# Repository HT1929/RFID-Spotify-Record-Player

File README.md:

# RFID-Spotify-Record-Player
Instead of vinyl records, RFID chips embedded in custom-made mini-records will trigger specific Spotify songs via a Raspberry Pi. The system mimics the action of placing a record on a turntable, offering both a visual spinning effect and the vast music library of Spotify.

# Project Overview
The RFID Spotify Record Player allows users to:
- Play, pause, skip and control volume for Spotify tracks.
- Select songs or playlists through a physical interface using the RFID sensor.
- Output audio through a built-in speaker system.
- Watch a disk spin as if it were playing a vinyl record, adding to the aesthetic of a traditional record player.

# Features
**User Interface:** Physical controls for playback and navigation.

**Controller:** Manages user inputs and communicates with Spotify.

**Network Module:** Connects to Wi-Fi to access the Spotify API.

**Spinning Disk:** A motorized disk spins to mimic the look of a record on a turntable.

**Spotify Integration:** Streams music directly from Spotify using the Spotify API.

**Audio Output:** Plays audio through connected speakers.

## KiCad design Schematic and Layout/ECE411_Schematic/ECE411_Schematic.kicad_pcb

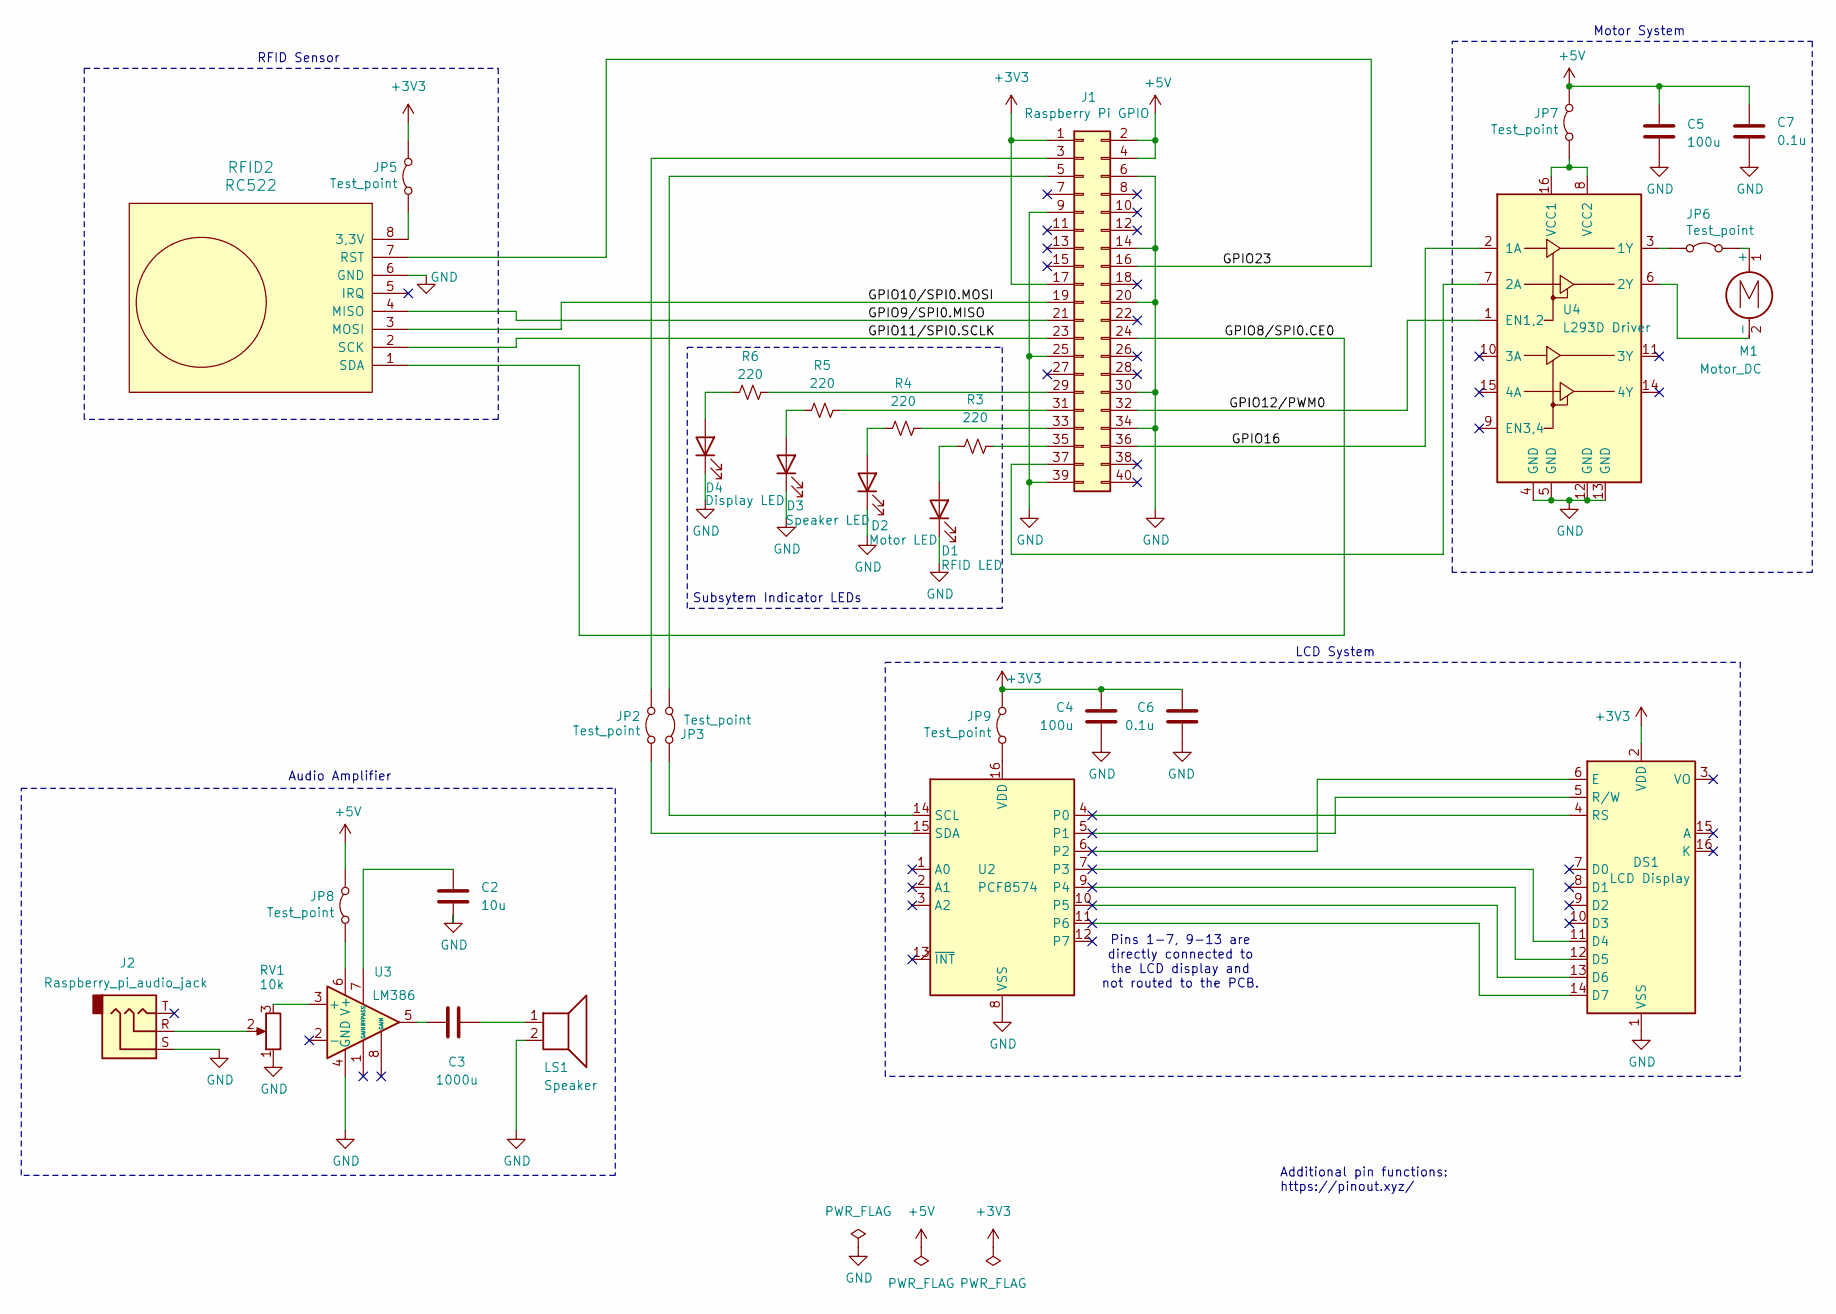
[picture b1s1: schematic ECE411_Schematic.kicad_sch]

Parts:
C2: 10u; C_Radial_D5.0mm_H11.0mm_P2.00mm
C3: 1000u; C_Radial_D10.0mm_H20.0mm_P5.00mm
C4, C5: 100u; C_0805_2012Metric_Pad1.18x1.45mm_HandSolder
C6, C7: 0.1u; C_0805_2012Metric_Pad1.18x1.45mm_HandSolder
D1: RFID LED; LED_Yuji_5730
D2: Motor LED; LED_Yuji_5730
D3: Speaker LED; LED_Yuji_5730
D4: Display LED; LED_Yuji_5730
DS1: LCD Display
J1: Raspberry Pi GPIO; PinSocket_2x20_P2.54mm_Vertical
J2: Raspberry_pi_audio_jack
JP2, JP3, JP5, JP6, JP7, JP8, JP9: Test_point; R_Axial_DIN0204_L3.6mm_D1.6mm_P2.54mm_Vertical
LS1: Speaker
M1: Motor_DC; Motor
R3, R4, R5, R6: 220; R_0805_2012Metric_Pad1.20x1.40mm_HandSolder
RFID2: RC522
RV1: 10k; Potentiometer_Bourns_3299W_Vertical
U2: PCF8574; LCD1602
U3: LM386; DIP-8_W7.62mm
U4: L293D Driver; DIP-16_W7.62mm

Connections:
+3V3: C4.1, C6.1, DS1.2 (VDD), J1.1, J1.17, JP5.2 (B), JP9.2 (B)
+5V: C5.1, C7.1, J1.2, J1.4, JP7.2 (B), JP8.2 (B)
/GPIO8/SPI0.CE0: J1.24, RFID2.1 (SDA); also elsewhere on the board
/GPIO9/SPI0.MISO: J1.21, RFID2.4 (MISO); also elsewhere on the board
/GPIO10/SPI0.MOSI: J1.19, RFID2.3 (MOSI); also elsewhere on the board
/GPIO11/SPI0.SCLK: J1.23, RFID2.2 (SCK); also elsewhere on the board
/GPIO12/PWM0: J1.32, U4.1 (EN1,2)
/GPIO16: J1.36, U4.2 (1A)
/GPIO23: J1.16, RFID2.7 (RST); also elsewhere on the board
GND: C2.2, C4.2, C5.2, C6.2, C7.2, D1.1 (K), D2.1 (K), D3.1 (K), D4.1 (K), DS1.1 (VSS), J1.6, J1.9, J1.14, J1.20, J1.25, J1.30, J1.34, J1.39, J2.S, LS1.2, RFID2.6 (GND), RV1.1, U2.8 (VSS), U3.4 (GND), U4.4 (GND), U4.5 (GND), U4.12 (GND), U4.13 (GND); also elsewhere on the board
unnamed: C3.1, U3.5
unnamed: C3.2, LS1.1
unnamed: D1.2 (A), R3.1
unnamed: D2.2 (A), R4.1
unnamed: D3.2 (A), R5.1
unnamed: D4.2 (A), R6.1
unnamed: DS1.4 (RS), U2.4 (P0)
unnamed: DS1.5 (R/W), U2.5 (P1)
unnamed: DS1.6 (E), U2.6 (P2)
unnamed: DS1.11 (D4), U2.7 (P3)
unnamed: DS1.12 (D5), U2.9 (P4)
unnamed: DS1.13 (D6), U2.10 (P5)
unnamed: DS1.14 (D7), U2.11 (P6)
unnamed: J1.3, JP2.2 (B)
unnamed: J1.5, JP3.1 (A)
unnamed: J1.29, R6.2
unnamed: J1.31, R5.2
unnamed: J1.33, R4.2
unnamed: J1.35, R3.2
unnamed: J1.37, U4.7 (2A)
unnamed: JP2.1 (A), U2.15 (SDA)
unnamed: JP3.2 (B), U2.14 (SCL)
unnamed 32: JP5.1 (A), RFID2.8 (3,3V); also elsewhere on the board
unnamed: JP6.1 (A), U4.3 (1Y)
unnamed: JP6.2 (B), M1.1 (+)
unnamed: JP7.1 (A), U4.8 (VCC2), U4.16 (VCC1)
unnamed: JP8.1 (A), U3.6 (V+)
unnamed: JP9.1 (A), U2.16 (VDD)
unnamed: M1.2 (-), U4.6 (2Y)
unnamed: J2.R, RV1.2
unnamed: RV1.3, U3.3 (+)
unnamed: C2.1, U3.7 (BYPASS)

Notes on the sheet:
RFID Sensor
LCD System
Additional pin functions: https://pinout.xyz/
Audio Amplifier
Motor System
Pins 1-7, 9-13 are directly connected to the LCD display and not routed to the PCB.
Subsytem Indicator LEDs

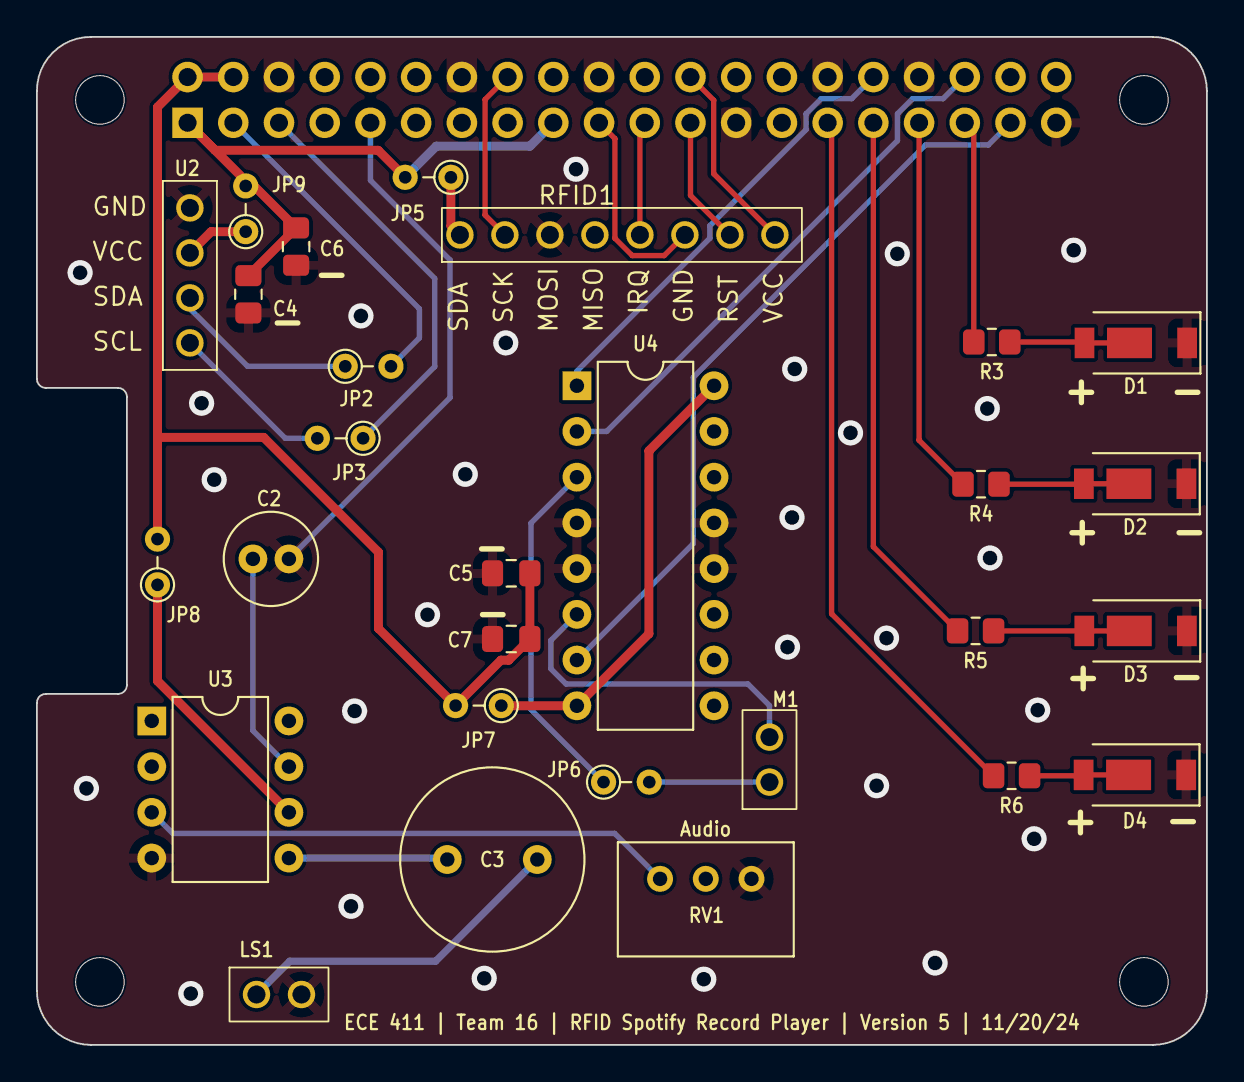
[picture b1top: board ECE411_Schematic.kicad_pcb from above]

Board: 2 copper layers, 65.0 x 56.0 mm, 33 parts (1 on the bottom side), 34 nets.

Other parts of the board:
MH1, MH2, MH3, MH4: MountingHole_2.7mm_M2.5
RFID1: RC522

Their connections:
/GPIO8/SPI0.CE0: RFID1.1 (SDA); also elsewhere on the board
/GPIO9/SPI0.MISO: RFID1.4 (MISO); also elsewhere on the board
/GPIO10/SPI0.MOSI: RFID1.3 (MOSI); also elsewhere on the board
/GPIO11/SPI0.SCLK: RFID1.2 (SCK); also elsewhere on the board
/GPIO23: RFID1.7 (RST); also elsewhere on the board
GND: RFID1.6 (GND); also elsewhere on the board
unnamed 32: RFID1.8 (3,3V); also elsewhere on the board

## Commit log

2024-11-02 Add files via upload
    Added major components with the appropriate connections to the Raspberry Pi. Still need to adjust the layout and see how it looks in PCB view.
2024-11-05 PDS version 2
    Made changes to the L0 and L1 diagrams
2024-11-05 Test the Spotify API connection through wifi and test with music
2024-11-06 Add files via upload
    Code for Raspberry Pi
2024-11-06 Rename ECE 411 Gant Chart.png to Gantt_Chart/ECE 411 Gant Chart.png
    a folder for the Gantt chart picture and code
2024-11-06 Update and rename ECE 411 Gant Chart.gan to Gantt_Chart/ECE 411 Gant Chart.gan
    add to folder
2024-11-07 Updated schematic
    Added in parts that was tested and worked on the device we are currently building.
2024-11-07 Create player.py
    Add a folder for all the codes
2024-11-07 Rename spotifyTest.py to Code/spotifyTest.py
2024-11-07 Preliminary layout of the PCB
2024-11-07 Current progress on the project with video demo
2024-11-14 Rename ECE411_Preliminary_Schematic.pdf to Schematic and Layout/ECE411_Preliminary_Schematic.pdf
2024-11-14 Add files via upload
    Third version of the schematic. Added no connect instead of remove the pins entirely. Also added the LCD circuit.
2024-11-14 Rename ECE411_Layout.pdf to Schematic and Layout/ECE411_Layout.pdf
2024-11-14 Add files via upload
    Second version of the schematic layout. Added the LCD screen connection and finished all the connections for all other components.
2024-11-17 KiCad Project Files
2024-11-17 added LEDs to indicate functioning subsystems
2024-11-19 Added test points, and subsystem led indicators
2024-11-19 Create deleteME.txt
    delete after uploading real files
2024-11-19 Add files via upload
    Case for RPi, RFID, motor, amp PCB - Rev 1
2024-11-19 Added SMD components to the PCB and rerouted a few traces
2024-11-19 Version 5 schematic and layout
2024-11-20 Version 6 schematic and Version 4 Layout
2024-11-20 Version 6 Schematic
2024-11-21 Final layout and schematic
2024-11-22 added a database to store the RFID IDs, motor, and speaker for audio output
2024-11-22 Create temp.py
    temporary file with old codes
2024-11-22 reedited
2024-11-22 redid the code for a smoother execution for each action
2024-11-22 renamed temp file
2024-12-05 version 4
2024-12-05 Rename Hierarchical Test.pdf to Test Plans/Hierarchical Test.pdf
2024-12-06 Add files via upload
    Test Plan Hierarchy, and 2 test plans with their results.
2024-12-06 Create LEDs
2024-12-06 made changes to RFID to play album instead of songs
2024-12-06 changes to main code
2024-12-06 more changes
